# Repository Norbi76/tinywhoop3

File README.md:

Adresa repository: https://github.com/Norbi76/tinywhoop3.git

Pentru a putea compila proiectele este necesara instalarea ESP IDF v6.0.2 !!
Fiecare dintre cele 2 proiecte se va compila si scrie pe micro separat.
Mediul de dezvolatare ESP IDF a fost utilizat pe Linux(Ubuntu).

Pasii pentru compilare si scriere: 
1. cd ~/.espressif/v6.0.2/esp-idf
2. . ./export.sh
3. cd tinywhoop3/flight_controller/ sau cd tinywhoop3/telemetry_module/ 
4. idf.py set-target esp32s3
5. idf.py build flash monitor

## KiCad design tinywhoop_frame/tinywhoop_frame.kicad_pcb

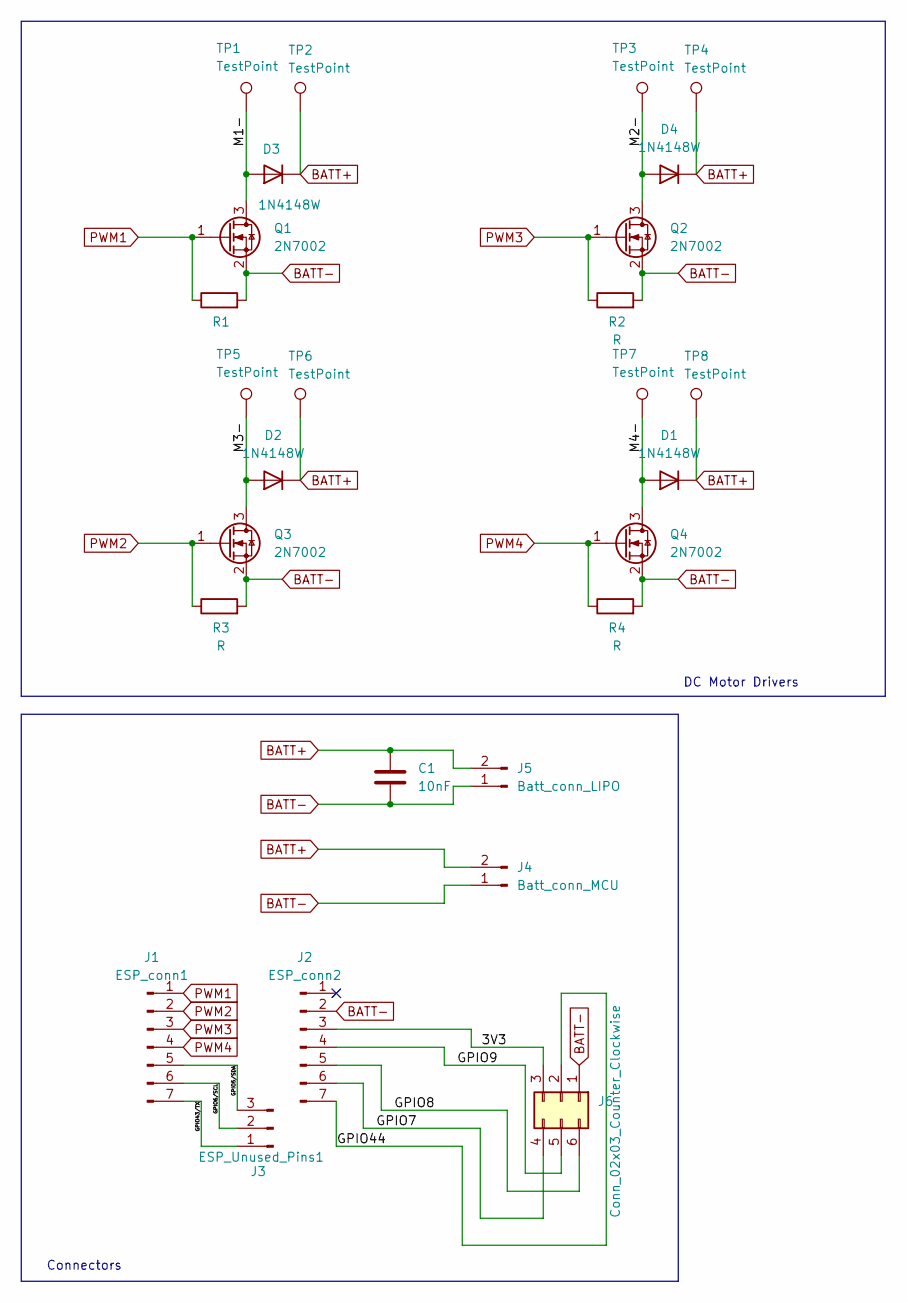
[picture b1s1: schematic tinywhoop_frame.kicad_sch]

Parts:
C1: 10nF; C_0805_2012Metric_Pad1.18x1.45mm_HandSolder
D1, D2, D3, D4: 1N4148W; D_SOD-123
J1: ESP_conn1; PinHeader_1x07_P2.54mm_Vertical
J2: ESP_conn2; PinHeader_1x07_P2.54mm_Vertical
J3: ESP_Unused_Pins1; PinHeader_1x03_P2.54mm_Vertical
J4: Batt_conn_MCU; PinHeader_1x02_P2.54mm_Vertical
J5: Batt_conn_LIPO; PinHeader_1x02_P2.54mm_Vertical
J6: Conn_02x03_Counter_Clockwise; PinSocket_2x03_P2.54mm_Vertical
Q1, Q2, Q3, Q4: 2N7002; SOT-23
R1, R2, R3, R4: R; R_0805_2012Metric
TP1, TP2, TP3, TP4, TP5, TP6, TP7, TP8: TestPoint; TestPoint_Pad_1.5x1.5mm

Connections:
/3V3: J2.3, J6.3
/GPIO5/SDA: J1.5, J3.3
/GPIO6/SCL: J1.6, J3.2
/GPIO7: J2.6, J6.4
/GPIO8: J2.5, J6.6
/GPIO9: J2.4, J6.5
/GPIO43/TX: J1.7, J3.1
/GPIO44: J2.7, J6.2
/M1-: D3.2 (A), Q1.3 (D), TP1.1
/M2-: D4.2 (A), Q2.3 (D), TP3.1
/M3-: D2.2 (A), Q3.3 (D), TP5.1
/M4-: D1.2 (A), Q4.3 (D), TP7.1
BATT+: C1.1, D1.1 (K), D2.1 (K), D3.1 (K), D4.1 (K), J4.2, J5.2, TP2.1, TP4.1, TP6.1, TP8.1
BATT-: C1.2, J2.2, J4.1, J5.1, J6.1, Q1.2 (S), Q2.2 (S), Q3.2 (S), Q4.2 (S), R1.2, R2.2, R3.2, R4.2
PWM1: J1.1, Q1.1 (G), R1.1
PWM2: J1.2, Q3.1 (G), R3.1
PWM3: J1.3, Q2.1 (G), R2.1
PWM4: J1.4, Q4.1 (G), R4.1

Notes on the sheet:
DC Motor Drivers
Connectors

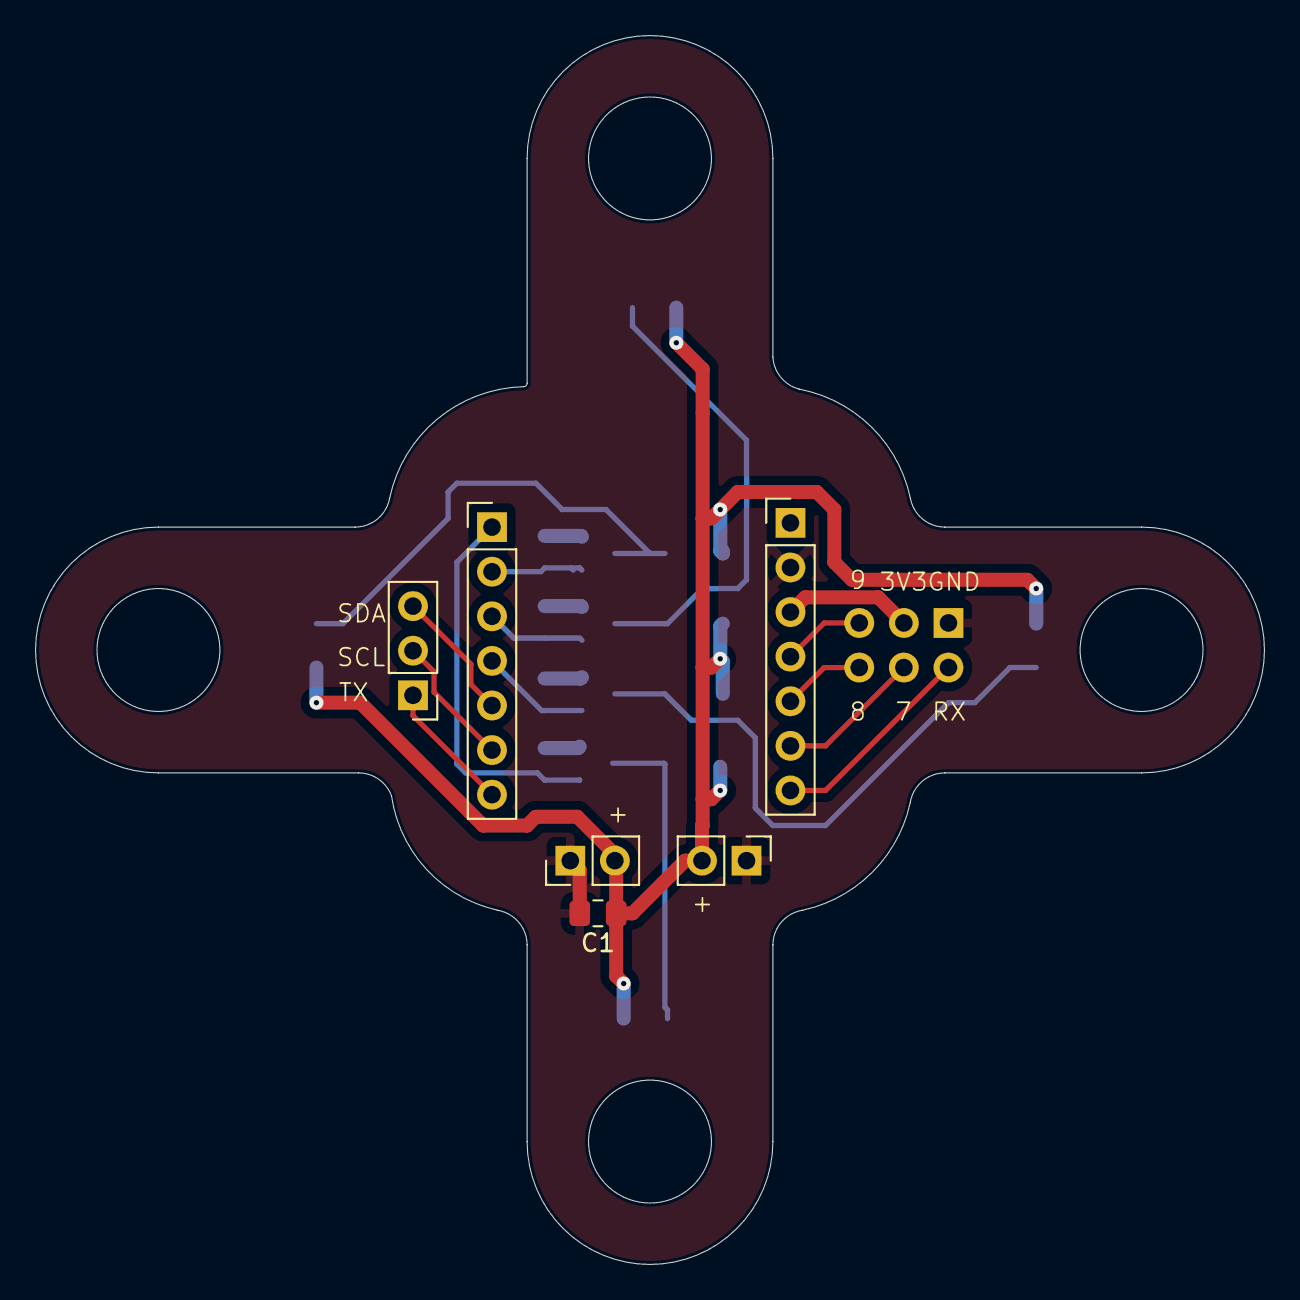
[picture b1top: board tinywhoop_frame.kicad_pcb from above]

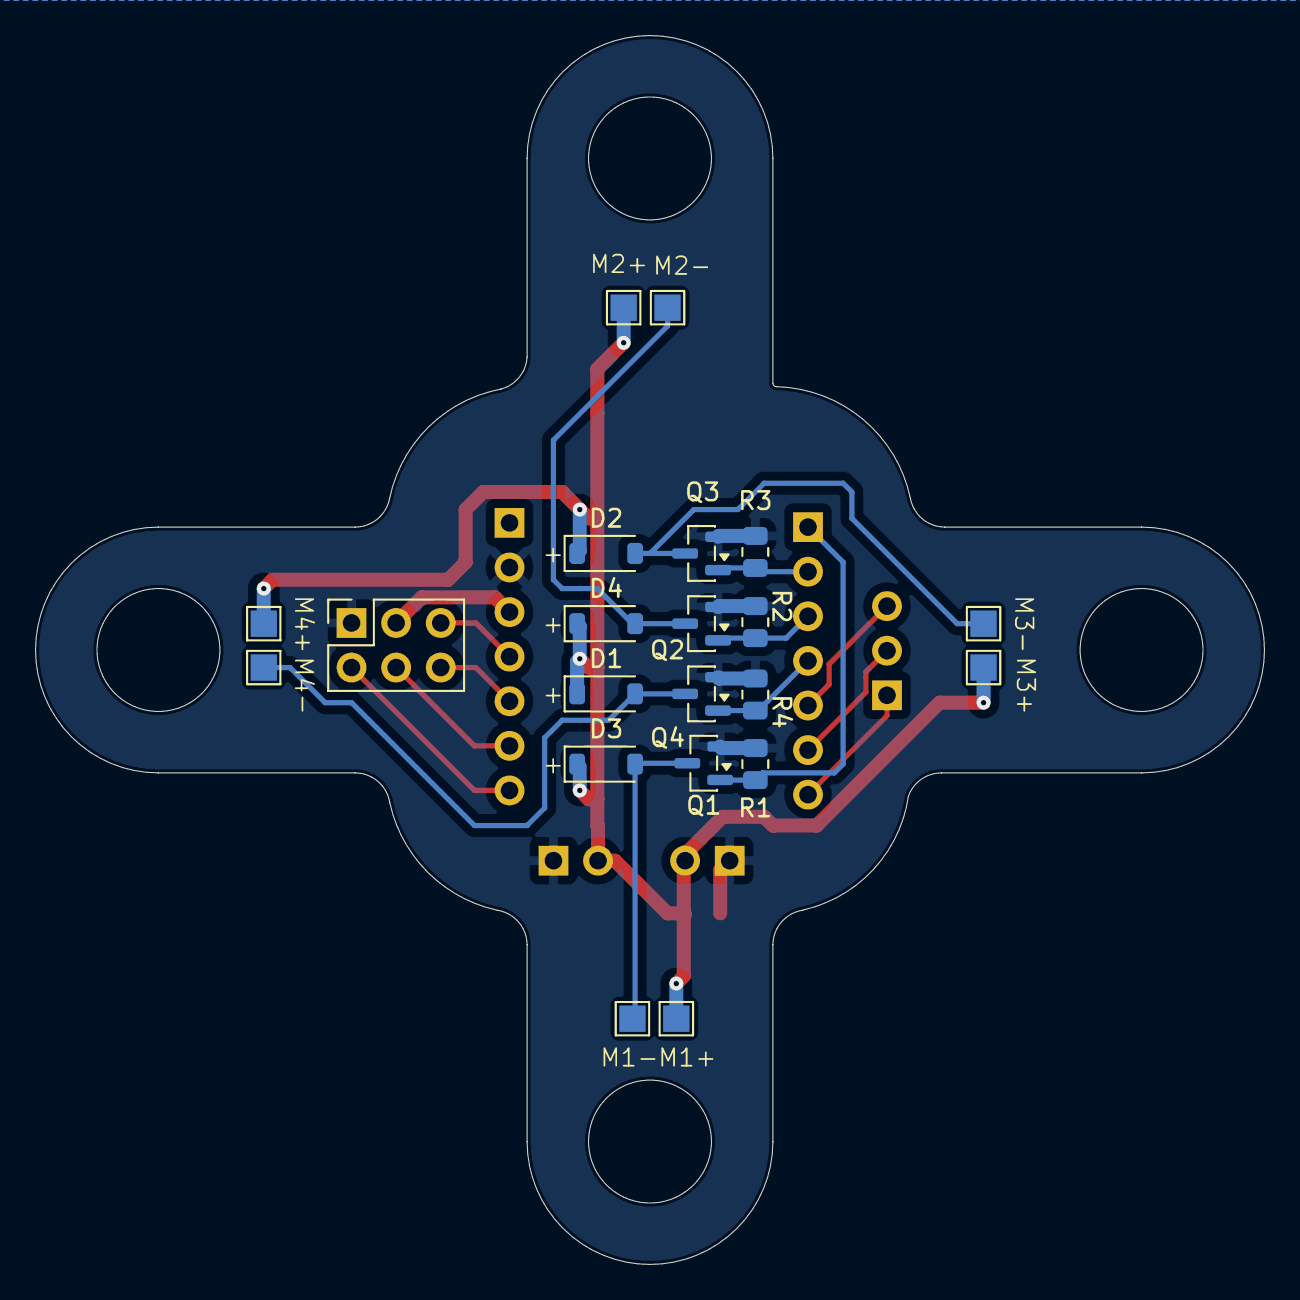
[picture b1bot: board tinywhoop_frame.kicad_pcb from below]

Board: 2 copper layers, 70.0 x 70.0 mm, 27 parts (21 on the bottom side), 18 nets.

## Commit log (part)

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2025-11-03 created ap and websocket which serves a webpage with a joystick
2025-11-04 moved ap functionality in a component
2025-11-10 implemented json parsing using cJson, fixed ws
2025-11-12 got 4 leds which i can control with 2 js s on a web page
2025-12-07 uploaded pcb kicad prj
2025-12-08 pcb updates, created fab files
2025-12-08 pcb updates
2025-12-10 updated pcb
2025-12-10 pcb update
2026-04-05 updated esp idf version to v6.0
